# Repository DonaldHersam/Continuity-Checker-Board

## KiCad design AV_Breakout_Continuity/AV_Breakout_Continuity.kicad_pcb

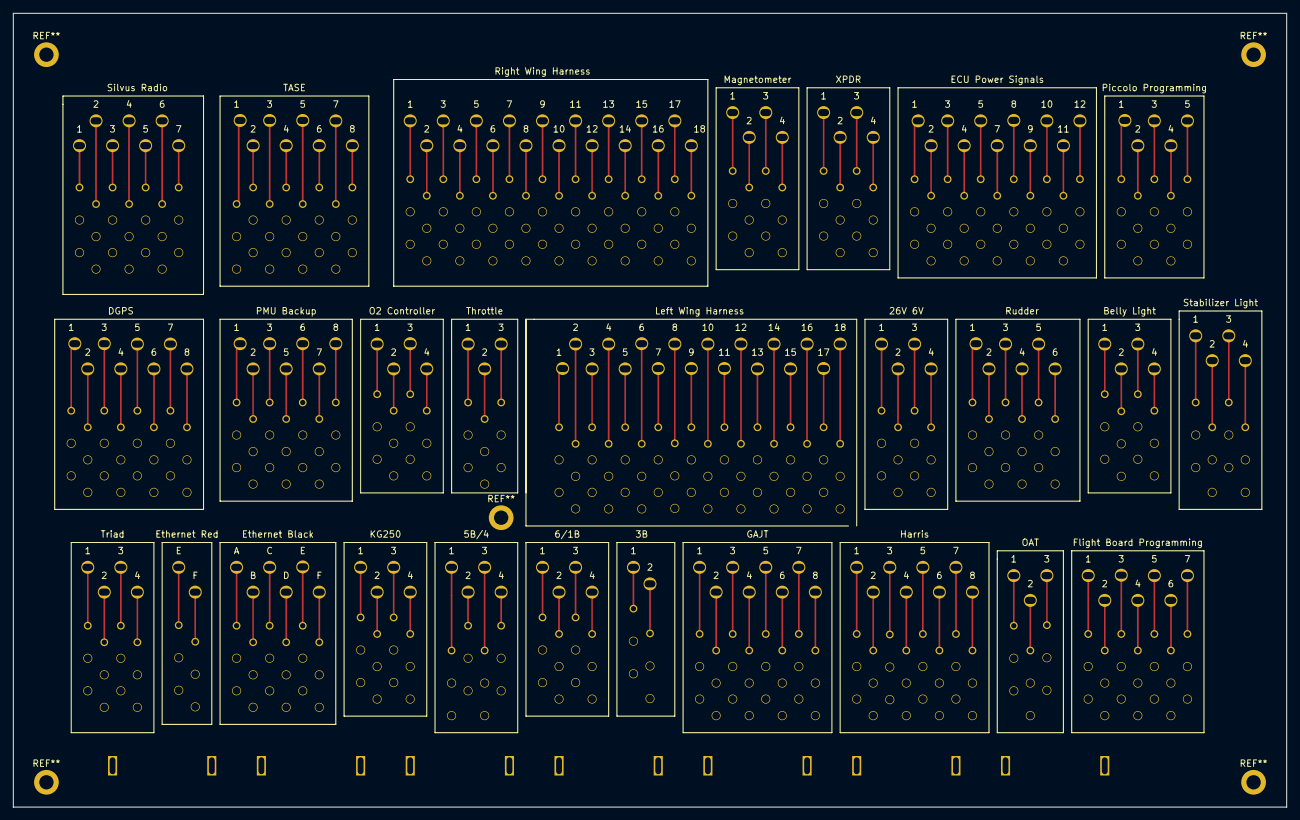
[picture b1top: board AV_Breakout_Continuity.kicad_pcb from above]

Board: 2 copper layers, 195.6 x 121.9 mm, 334 parts (0 on the bottom side), 167 nets.

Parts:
SR1, SR2, SR3, SR4, SR5, SR6, SR7, SR8, SR9, SR10, SR11, SR12, SR13, SR14, SR15, SR16, SR17, SR18, SR19, SR20, SR21, SR22, SR23, SR24, SR25, SR26, SR27, SR28, SR29, SR30, SR31, SR32, SR33, SR34, SR35, SR36, SR37, SR38, SR39, SR40, SR41, SR42, SR43, SR44, SR45, SR46, SR47, SR48, SR49, SR50, SR51, SR52, SR53, SR54, SR55, SR56, SR57, SR58, SR59, SR60, SR61, SR62, SR63, SR64, SR65, SR66, SR67, SR68, SR69, SR70, SR71, SR72, SR73, SR74, SR75, SR76, SR77, SR78, SR79, SR80, SR81, SR82, SR83, SR84, SR85, SR86, SR87, SR88, SR89, SR90, SR91, SR92, SR93, SR94, SR95, SR96, SR97, SR98, SR99, SR100, SR101, SR102, SR103, SR104, SR105, SR106, SR107, SR108, SR109, SR110, SR111, SR112, SR113, SR114, SR115, SR116, SR117, SR118, SR119, SR120, SR121, SR122, SR123, SR124, SR125, SR126, SR127, SR128, SR129, SR130, SR131, SR132, SR133, SR134, SR135, SR136, SR137, SR138, SR139, SR140, SR141, SR142, SR143, SR144, SR145, SR146, SR147, SR148, SR149, SR150, SR151, SR152, SR153, SR154, SR155, SR156, SR157, SR158, SR159, SR160, SR161, SR162, SR163, SR164, SR165, SR166, SR167: StrainRelief
TP1, TP2, TP3, TP4, TP5, TP6, TP7, TP8, TP9, TP10, TP11, TP12, TP13, TP14, TP15, TP16, TP17, TP18, TP19, TP20, TP21, TP22, TP23, TP24, TP25, TP26, TP27, TP28, TP29, TP30, TP31, TP32, TP33, TP34, TP35, TP36, TP37, TP38, TP39, TP40, TP41, TP42, TP43, TP44, TP45, TP46, TP47, TP48, TP49, TP50, TP51, TP52, TP53, TP54, TP55, TP56, TP57, TP58, TP59, TP60, TP61, TP62, TP63, TP64, TP65, TP66, TP67, TP68, TP69, TP70, TP71, TP72, TP73, TP74, TP75, TP76, TP77, TP78, TP79, TP80, TP81, TP82, TP83, TP84, TP85, TP86, TP87, TP88, TP89, TP90, TP91, TP92, TP93, TP94, TP95, TP96, TP97, TP98, TP99, TP100, TP101, TP102, TP103, TP104, TP105, TP106, TP107, TP108, TP109, TP110, TP111, TP112, TP113, TP114, TP115, TP116, TP117, TP118, TP119, TP120, TP121, TP122, TP123, TP124, TP125, TP126, TP127, TP128, TP129, TP130, TP131, TP132, TP133, TP134, TP135, TP136, TP137, TP138, TP139, TP140, TP141, TP142, TP143, TP144, TP145, TP146, TP147, TP148, TP149, TP150, TP151, TP152, TP153, TP154, TP155, TP156, TP157, TP158, TP159, TP160, TP161, TP162, TP163, TP164, TP165, TP166, TP167: 36-5029CT-ND; TestPoint

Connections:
unnamed: SR1.1, TP1.1
unnamed: SR2.1, TP2.1
unnamed: SR3.1, TP3.1
unnamed: SR4.1, TP4.1
unnamed: SR5.1, TP5.1
unnamed: SR6.1, TP6.1
unnamed: SR7.1, TP7.1
unnamed: SR8.1, TP8.1
unnamed: SR9.1, TP9.1
unnamed: SR10.1, TP10.1
unnamed: SR11.1, TP11.1
unnamed: SR12.1, TP12.1
unnamed: SR13.1, TP13.1
unnamed: SR14.1, TP14.1
unnamed: SR15.1, TP15.1
unnamed: SR16.1, TP16.1
unnamed: SR17.1, TP17.1
unnamed: SR18.1, TP18.1
unnamed: SR19.1, TP19.1
unnamed: SR20.1, TP20.1
unnamed: SR21.1, TP21.1
unnamed: SR22.1, TP22.1
unnamed: SR23.1, TP23.1
unnamed: SR24.1, TP24.1
unnamed: SR25.1, TP25.1
unnamed: SR26.1, TP26.1
unnamed: SR27.1, TP27.1
unnamed: SR28.1, TP28.1
unnamed: SR29.1, TP29.1
unnamed: SR30.1, TP30.1
unnamed: SR31.1, TP31.1
unnamed: SR32.1, TP32.1
unnamed: SR33.1, TP33.1
unnamed: SR34.1, TP34.1
unnamed: SR35.1, TP35.1
unnamed: SR36.1, TP36.1
unnamed: SR37.1, TP37.1
unnamed: SR38.1, TP38.1
unnamed: SR39.1, TP39.1
unnamed: SR40.1, TP40.1
unnamed: SR41.1, TP41.1
unnamed: SR42.1, TP42.1
unnamed: SR43.1, TP43.1
unnamed: SR44.1, TP44.1
unnamed: SR45.1, TP45.1
unnamed: SR46.1, TP46.1
unnamed: SR47.1, TP47.1
unnamed: SR48.1, TP48.1
unnamed: SR49.1, TP49.1
unnamed: SR50.1, TP50.1
unnamed: SR51.1, TP51.1
unnamed: SR52.1, TP52.1
unnamed: SR53.1, TP53.1
unnamed: SR54.1, TP54.1
unnamed: SR55.1, TP55.1
unnamed: SR56.1, TP56.1
unnamed: SR57.1, TP57.1
unnamed: SR58.1, TP58.1
unnamed: SR59.1, TP59.1
unnamed: SR60.1, TP60.1
unnamed: SR61.1, TP61.1
unnamed: SR62.1, TP62.1
unnamed: SR63.1, TP63.1
unnamed: SR64.1, TP64.1
unnamed: SR65.1, TP65.1
unnamed: SR66.1, TP66.1
unnamed: SR67.1, TP67.1
unnamed: SR68.1, TP68.1
unnamed: SR69.1, TP69.1
unnamed: SR70.1, TP70.1
unnamed: SR71.1, TP71.1
unnamed: SR72.1, TP72.1
unnamed: SR73.1, TP73.1
unnamed: SR74.1, TP74.1
unnamed: SR75.1, TP75.1
unnamed: SR76.1, TP76.1
unnamed: SR77.1, TP77.1
unnamed: SR78.1, TP78.1
unnamed: SR79.1, TP79.1
unnamed: SR80.1, TP80.1
unnamed: SR81.1, TP81.1
unnamed: SR82.1, TP82.1
unnamed: SR83.1, TP83.1
unnamed: SR84.1, TP84.1
unnamed: SR85.1, TP85.1
unnamed: SR86.1, TP86.1
unnamed: SR87.1, TP87.1
unnamed: SR88.1, TP88.1
unnamed: SR89.1, TP89.1
unnamed: SR90.1, TP90.1
unnamed: SR91.1, TP91.1
unnamed: SR92.1, TP92.1
unnamed: SR93.1, TP93.1
unnamed: SR94.1, TP94.1
unnamed: SR95.1, TP95.1
unnamed: SR96.1, TP96.1
unnamed: SR97.1, TP97.1
unnamed: SR98.1, TP98.1
unnamed: SR99.1, TP99.1
unnamed: SR100.1, TP100.1
unnamed: SR101.1, TP101.1
unnamed: SR102.1, TP102.1
unnamed: SR103.1, TP103.1
unnamed: SR104.1, TP104.1
unnamed: SR105.1, TP105.1
unnamed: SR106.1, TP106.1
unnamed: SR107.1, TP107.1
unnamed: SR108.1, TP108.1
unnamed: SR109.1, TP109.1
unnamed: SR110.1, TP110.1
unnamed: SR111.1, TP111.1
unnamed: SR112.1, TP112.1
unnamed: SR113.1, TP113.1
unnamed: SR114.1, TP114.1
unnamed: SR115.1, TP115.1
unnamed: SR116.1, TP116.1
unnamed: SR117.1, TP117.1
unnamed: SR118.1, TP118.1
unnamed: SR119.1, TP119.1
unnamed: SR120.1, TP120.1
unnamed: SR121.1, TP121.1
unnamed: SR122.1, TP122.1
unnamed: SR123.1, TP123.1
unnamed: SR124.1, TP124.1
unnamed: SR125.1, TP125.1
unnamed: SR126.1, TP126.1
unnamed: SR127.1, TP127.1
unnamed: SR128.1, TP128.1
unnamed: SR129.1, TP129.1
unnamed: SR130.1, TP130.1
unnamed: SR131.1, TP131.1
unnamed: SR132.1, TP132.1
unnamed: SR133.1, TP133.1
unnamed: SR134.1, TP134.1
unnamed: SR135.1, TP135.1
unnamed: SR136.1, TP136.1
unnamed: SR137.1, TP137.1
unnamed: SR138.1, TP138.1
unnamed: SR139.1, TP139.1
unnamed: SR140.1, TP140.1
unnamed: SR141.1, TP141.1
unnamed: SR142.1, TP142.1
unnamed: SR143.1, TP143.1
unnamed: SR144.1, TP144.1
unnamed: SR145.1, TP145.1
unnamed: SR146.1, TP146.1
unnamed: SR147.1, TP147.1
unnamed: SR148.1, TP148.1
unnamed: SR149.1, TP149.1
unnamed: SR150.1, TP150.1
unnamed: SR151.1, TP151.1
unnamed: SR152.1, TP152.1
unnamed: SR153.1, TP153.1
unnamed: SR154.1, TP154.1
unnamed: SR155.1, TP155.1
unnamed: SR156.1, TP156.1
unnamed: SR157.1, TP157.1
unnamed: SR158.1, TP158.1
unnamed: SR159.1, TP159.1
unnamed: SR160.1, TP160.1
unnamed: SR161.1, TP161.1
unnamed: SR162.1, TP162.1
unnamed: SR163.1, TP163.1
unnamed: SR164.1, TP164.1
unnamed: SR165.1, TP165.1
unnamed: SR166.1, TP166.1
unnamed: SR167.1, TP167.1

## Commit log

2019-04-16 Add kicad and project files
2019-04-16 update to csv
2019-04-16 Start to pcb routing
2019-04-16 Last commit of the day
2019-04-19 update to schematics
2019-04-22 update to schematic
2019-04-25 add appropriate spaces to board layout
2019-04-25 routed all connector breakouts
2019-04-26 massive edits to pcb and schematics
2019-04-26 add to schematics
2019-04-29 remove all erc errors
2019-04-29 edit to libs
2019-04-30 configure rats nest in pcb view
2019-04-30 start organizing footprints
2019-05-02 organize all breakouts on pcb
2019-05-07 add new pcb layers
2019-05-07 convert all test points to through hole
2019-05-09 update board
2019-05-13 remove all designators
2019-05-13 annotate pcb
2019-05-14 done?
